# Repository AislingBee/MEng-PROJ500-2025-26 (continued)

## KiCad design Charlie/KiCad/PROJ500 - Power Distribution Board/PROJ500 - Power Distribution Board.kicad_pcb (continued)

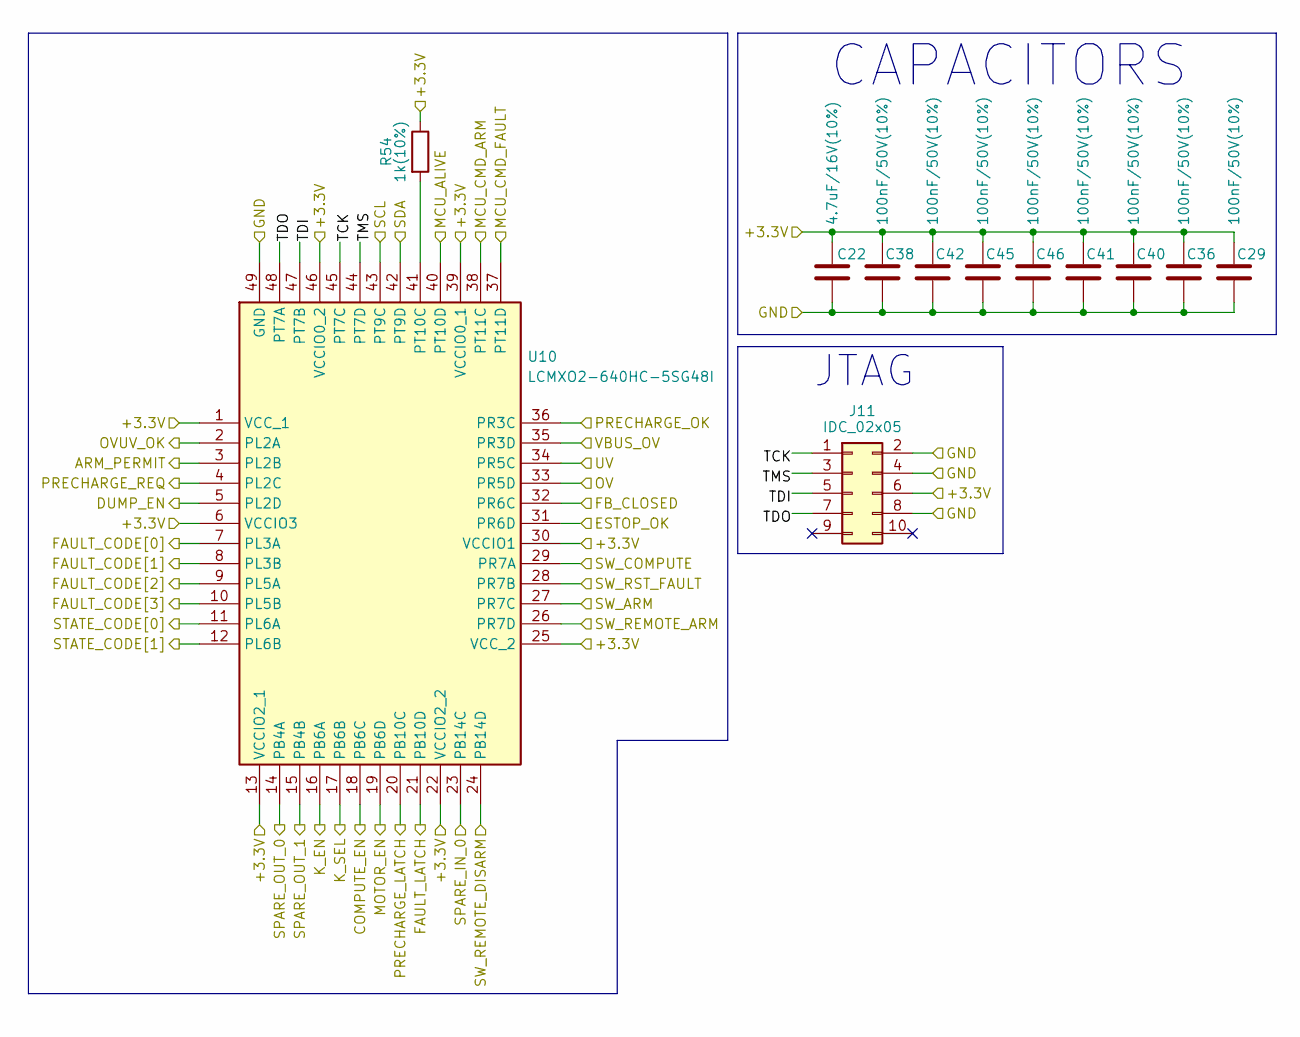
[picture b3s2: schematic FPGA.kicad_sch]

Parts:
C22: 4.7uF/16V(10%); C_0805_2012Metric
C29, C36, C38, C40, C41, C42, C45, C46: 100nF/50V(10%); C_0402_1005Metric
J11: IDC_02x05; IDC-Header_2x05_P2.54mm_Vertical
R54: 1k(10%); R_0402_1005Metric
U10: LCMXO2-640HC-5SG48I; QFN50P700X700X100-49N-D; Mouser Part Number 842-MXO2640HC5SG48I

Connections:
+3.3V: C22.1, C29.2, C36.2, C38.2, C40.2, C41.2, C42.2, C45.2, C46.2, J11.6, R54.1, U10.1 (VCC_1), U10.6 (VCCIO3), U10.13 (VCCIO2_1), U10.22 (VCCIO2_2), U10.25 (VCC_2), U10.30 (VCCIO1), U10.39 (VCCIO0_1), U10.46 (VCCIO0_2); also elsewhere on the board
/ARM_PERMIT: U10.3 (PL2B)
/BUS_OV: U10.35 (PR3D); also elsewhere on the board
/COMPUTE_EN: U10.18 (PB6C); also elsewhere on the board
/DUMP_EN: U10.5 (PL2D)
/ESTOP_OK_BUF: U10.31 (PR6D); also elsewhere on the board
/FAULT_LATCH: U10.21 (PB10D); also elsewhere on the board
/FPGA/PRECHARGE_REQ: U10.4 (PL2C)
/FPGA/SPARE_IN_0: U10.23 (PB14C)
/FPGA/TCK: J11.1, U10.45 (PT7C)
/FPGA/TDI: J11.5, U10.47 (PT7B)
/FPGA/TDO: J11.7, U10.48 (PT7A)
/FPGA/TMS: J11.3, U10.44 (PT7D)
/FPGA_FC_0: U10.7 (PL3A); also elsewhere on the board
/FPGA_FC_1: U10.8 (PL3B); also elsewhere on the board
/FPGA_FC_2: U10.9 (PL5A); also elsewhere on the board
/FPGA_FC_3: U10.10 (PL5B); also elsewhere on the board
/FPGA_SC_0: U10.11 (PL6A); also elsewhere on the board
/FPGA_SC_1: U10.12 (PL6B); also elsewhere on the board
/FPGA_SPARE_OUT_0: U10.14 (PB4A); also elsewhere on the board
/FPGA_SPARE_OUT_1: U10.15 (PB4B); also elsewhere on the board
/K_EN: U10.16 (PB6A); also elsewhere on the board
/K_SEL: U10.17 (PB6B); also elsewhere on the board
/MCU_ALIVE: U10.40 (PT10D); also elsewhere on the board
/MCU_CMD_ARM: U10.38 (PT11C); also elsewhere on the board
/MCU_CMD_FAULT: U10.37 (PT11D); also elsewhere on the board
/MOTOR_CONT_EN: U10.19 (PB6D); also elsewhere on the board
/MOTOR_CONT_FB: U10.32 (PR6C); also elsewhere on the board
/OVUV_OK: U10.2 (PL2A)
/PRECHARGE_LATCH: U10.20 (PB10C)
/PRECHARGE_OK: U10.36 (PR3C); also elsewhere on the board
/SCL: U10.43 (PT9C); also elsewhere on the board
/SDA: U10.42 (PT9D); also elsewhere on the board
/SOURCE_OV: U10.33 (PR5D); also elsewhere on the board
/SOURCE_UV: U10.34 (PR5C); also elsewhere on the board
/SW_ARM_BUF: U10.27 (PR7C); also elsewhere on the board
/SW_COMPUTE_BUF: U10.29 (PR7A); also elsewhere on the board
/SW_REMOTE_ARM_BUF: U10.26 (PR7D); also elsewhere on the board
/SW_REMOTE_DISARM_BUF: U10.24 (PB14D); also elsewhere on the board
/SW_RST_FAULT_BUF: U10.28 (PR7B); also elsewhere on the board
GND: C22.2, C29.1, C36.1, C38.1, C40.1, C41.1, C42.1, C45.1, C46.1, J11.2, J11.4, J11.8, U10.49 (GND); also elsewhere on the board
unnamed: R54.2, U10.41 (PT10C)

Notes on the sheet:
JTAG
CAPACITORS

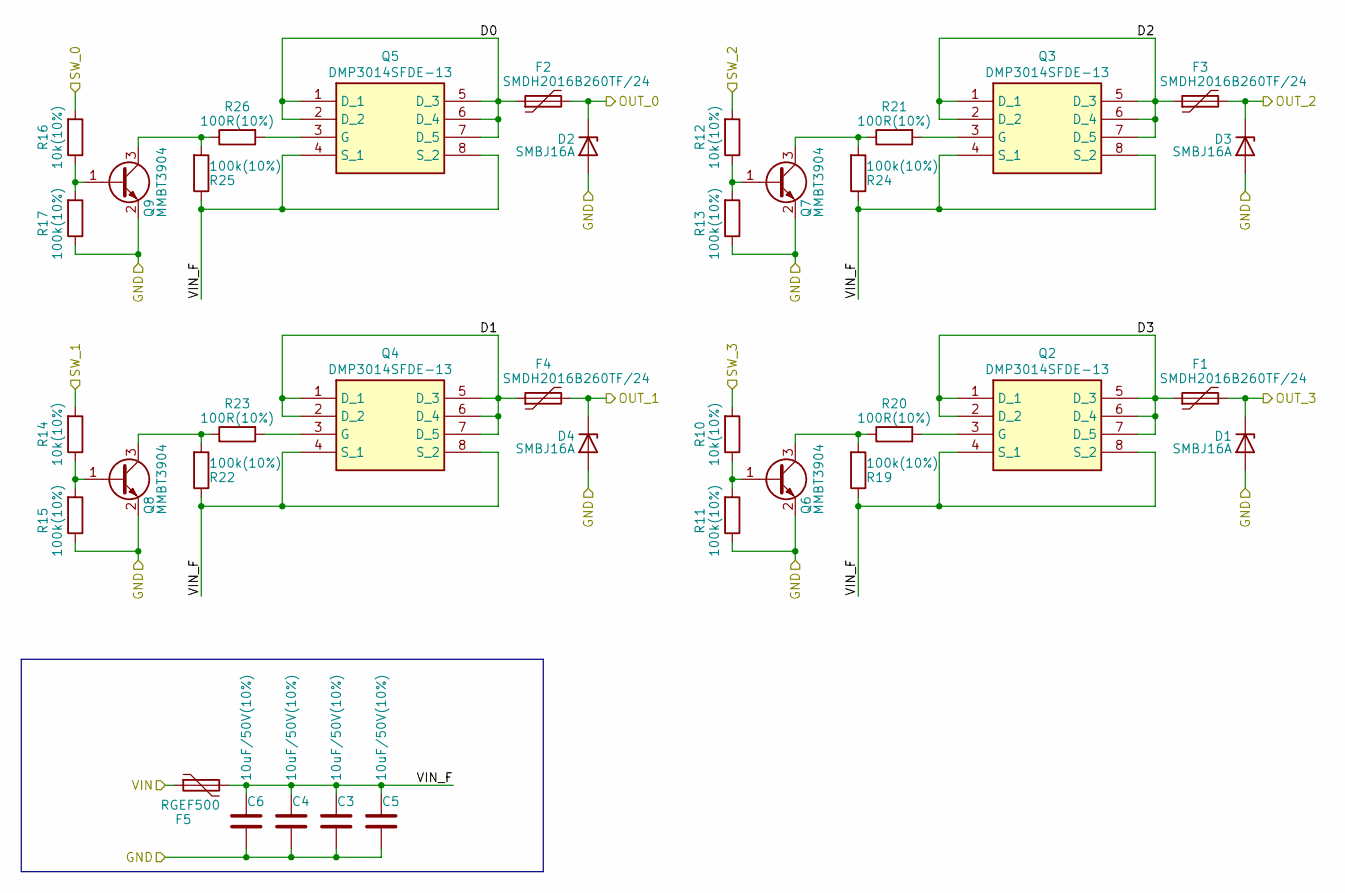
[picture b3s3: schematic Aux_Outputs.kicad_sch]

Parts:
C3, C4, C5, C6: 10uF/50V(10%); C_1206_3216Metric
D1, D2, D3, D4: SMBJ16A; D_SMB
F1, F2, F3, F4: SMDH2016B260TF/24; FUSC5141X160N
F5: RGEF500
Q2, Q3, Q4, Q5: DMP3014SFDE-13; DMP1022UFDEQ7; Manufacturer_Part_Number DMP3014SFDE-13
Q6, Q7, Q8, Q9: MMBT3904; SOT-23
R10, R12, R14, R16: 10k(10%); R_0402_1005Metric
R11, R13, R15, R17, R19, R22, R24, R25: 100k(10%); R_0402_1005Metric
R20, R21, R23, R26: 100R(10%); R_0402_1005Metric

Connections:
12V_SW: F5.1; also elsewhere on the board
/AUX_SW_0: R16.2; also elsewhere on the board
/AUX_SW_1: R14.2; also elsewhere on the board
/AUX_SW_2: R12.2; also elsewhere on the board
/AUX_SW_3: R10.2; also elsewhere on the board
/Aux Outputs/D0: F2.1, Q5.1 (D_1), Q5.2 (D_2), Q5.5 (D_3), Q5.6 (D_4), Q5.7 (D_5)
/Aux Outputs/D1: F4.1, Q4.1 (D_1), Q4.2 (D_2), Q4.5 (D_3), Q4.6 (D_4), Q4.7 (D_5)
/Aux Outputs/D2: F3.1, Q3.1 (D_1), Q3.2 (D_2), Q3.5 (D_3), Q3.6 (D_4), Q3.7 (D_5)
/Aux Outputs/D3: F1.1, Q2.1 (D_1), Q2.2 (D_2), Q2.5 (D_3), Q2.6 (D_4), Q2.7 (D_5)
/Aux Outputs/OUT_0: D2.1 (K), F2.2; also elsewhere on the board
/Aux Outputs/OUT_1: D4.1 (K), F4.2; also elsewhere on the board
/Aux Outputs/OUT_2: D3.1 (K), F3.2; also elsewhere on the board
/Aux Outputs/OUT_3: D1.1 (K), F1.2; also elsewhere on the board
/Aux Outputs/VIN_F: C3.1, C4.1, C5.1, C6.1, F5.2, Q2.4 (S_1), Q2.8 (S_2), Q3.4 (S_1), Q3.8 (S_2), Q4.4 (S_1), Q4.8 (S_2), Q5.4 (S_1), Q5.8 (S_2), R19.1, R22.1, R24.1, R25.1
GND: C3.2, C4.2, C5.2, C6.2, D1.2 (A), D2.2 (A), D3.2 (A), D4.2 (A), Q6.2 (E), Q7.2 (E), Q8.2 (E), Q9.2 (E), R11.1, R13.1, R15.1, R17.1; also elsewhere on the board
unnamed: Q2.3 (G), R20.2
unnamed: Q3.3 (G), R21.2
unnamed: Q4.3 (G), R23.2
unnamed: Q5.3 (G), R26.2
unnamed: Q6.1 (B), R10.1, R11.2
unnamed: Q6.3 (C), R19.2, R20.1
unnamed: Q7.1 (B), R12.1, R13.2
unnamed: Q7.3 (C), R21.1, R24.2
unnamed: Q8.1 (B), R14.1, R15.2
unnamed: Q8.3 (C), R22.2, R23.1
unnamed: Q9.1 (B), R16.1, R17.2
unnamed: Q9.3 (C), R25.2, R26.1

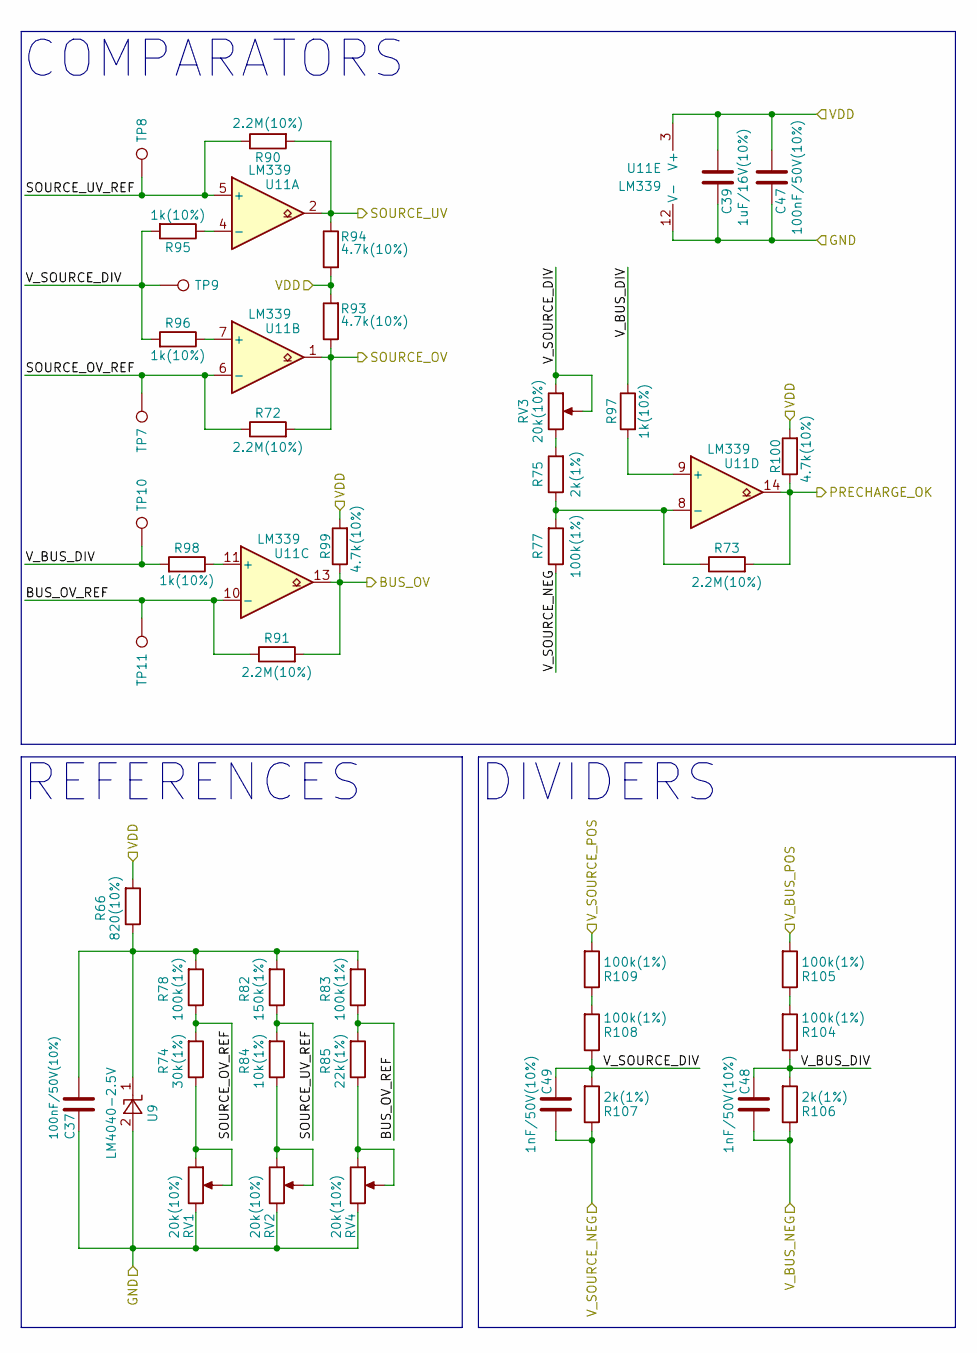
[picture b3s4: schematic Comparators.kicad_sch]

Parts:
C37, C47: 100nF/50V(10%); C_0402_1005Metric
C39: 1uF/16V(10%); C_0603_1608Metric
C48, C49: 1nF/50V(10%); C_0402_1005Metric
R66: 820(10%); R_0402_1005Metric
R72, R73, R90, R91: 2.2M(10%); R_0402_1005Metric
R74: 30k(1%); R_0402_1005Metric
R75, R106, R107: 2k(1%); R_0402_1005Metric
R77, R78, R83: 100k(1%); R_0402_1005Metric
R82: 150k(1%); R_0402_1005Metric
R84: 10k(1%); R_0402_1005Metric
R85: 22k(1%); R_0402_1005Metric
R93, R94, R99, R100: 4.7k(10%); R_0402_1005Metric
R95, R96, R97, R98: 1k(10%); R_0402_1005Metric
R104, R105, R108, R109: 100k(1%); R_0603_1608Metric
RV1, RV2, RV3, RV4: 20k(10%); Potentiometer_Bourns_3296Y_Vertical
TP7, TP8, TP9, TP10, TP11: TestPoint; TestPoint_Pad_D1.0mm
U9: LM4040-2.5V; TSOT-23; Part Number LM4040B25FTA
U11: LM339; TSSOP-14_4.4x5mm_P0.65mm

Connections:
+3.3VA: C39.2, C47.1, R66.2, R93.2, R94.2, R99.2, R100.2, U11.3 (V+); also elsewhere on the board
/BUS_OV: R91.2, R99.1, U11.13; also elsewhere on the board
/Comparators/BUS_OV_REF: R83.1, R85.2, R91.1, TP11.1, U11.10 (-)
/Comparators/SOURCE_OV_REF: R72.1, R74.2, R78.1, TP7.1, U11.6 (-)
/Comparators/SOURCE_UV_REF: R82.1, R84.2, R90.1, TP8.1, U11.5 (+)
/Comparators/V_BUS_DIV: C48.1, R97.1, R98.2, R104.1, R106.2, TP10.1
/Comparators/V_SOURCE_DIV: C49.1, R95.2, R96.2, R107.2, R108.1, RV3.1, RV3.2, TP9.1
/PRECHARGE_OK: R73.2, R100.1, U11.14; also elsewhere on the board
/SOURCE_OV: R72.2, R93.1, U11.1; also elsewhere on the board
/SOURCE_UV: R90.2, R94.1, U11.2; also elsewhere on the board
/V_BUS_POS: R105.2; also elsewhere on the board
/V_SENSE_NEG: C48.2, C49.2, R77.1, R106.1, R107.1; also elsewhere on the board
/V_SOURCE_POS: R109.2; also elsewhere on the board
GNDA: C37.2, C39.1, C47.2, RV1.3, RV2.3, RV4.3, U9.2 (A), U11.12 (V-); also elsewhere on the board
unnamed: R74.1, RV1.1, RV1.2
unnamed: R75.2, RV3.3
unnamed: R84.1, RV2.1, RV2.2
unnamed: R85.1, RV4.1, RV4.2
unnamed: R104.2, R105.1
unnamed: R108.2, R109.1
unnamed: C37.1, R66.1, R78.2, R82.2, R83.2, U9.1 (K)
unnamed: R95.1, U11.4 (-)
unnamed: R96.1, U11.7 (+)
unnamed: R98.1, U11.11 (+)
unnamed: R97.2, U11.9 (+)
unnamed: R73.1, R75.1, R77.2, U11.8 (-)

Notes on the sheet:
COMPARATORS
REFERENCES
DIVIDERS

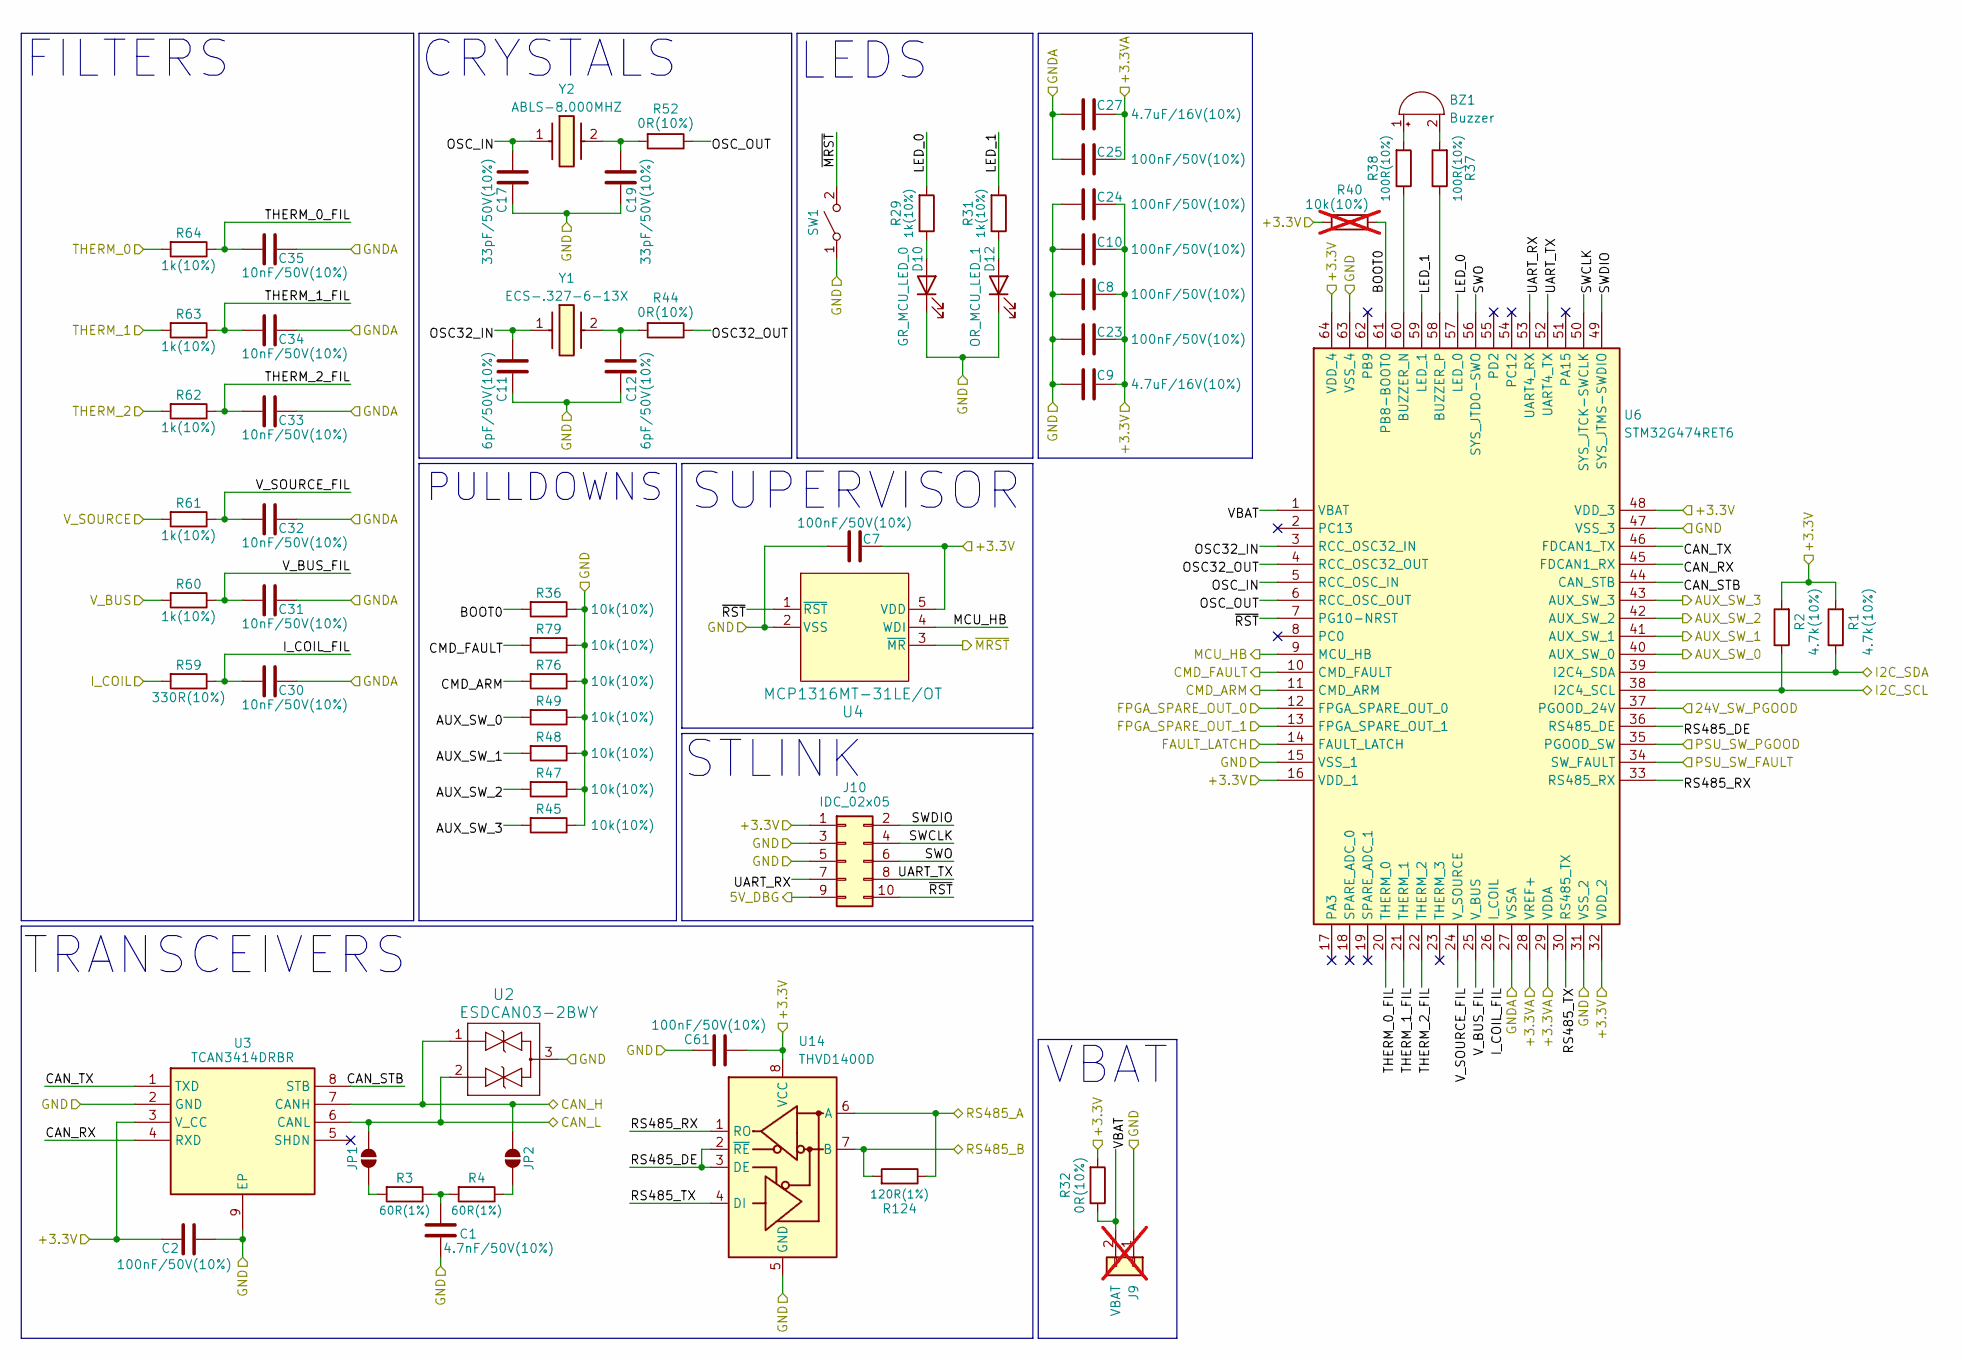
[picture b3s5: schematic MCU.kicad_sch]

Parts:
BZ1: Buzzer; C_Radial_D10.0mm_H12.5mm_P5.00mm
C1: 4.7nF/50V(10%); C_0402_1005Metric
C2, C7, C8, C10, C23, C24, C25, C61: 100nF/50V(10%); C_0402_1005Metric
C9, C27: 4.7uF/16V(10%); C_0805_2012Metric
C11, C12: 6pF/50V(10%); C_0402_1005Metric
C17, C19: 33pF/50V(10%); C_0402_1005Metric
C30, C31, C32, C33, C34, C35: 10nF/50V(10%); C_0402_1005Metric
D10: GR_MCU_LED_0; D_0805_2012Metric
D12: OR_MCU_LED_1; D_0805_2012Metric
J9: VBAT; PinHeader_1x02_P2.54mm_Vertical; Part Number 1-0201FBV0T; not fitted
J10: IDC_02x05; IDC-Header_2x05_P2.54mm_Vertical
JP1, JP2: SolderJumper_2_Open; SolderJumper-2_P1.3mm_Open_Pad1.0x1.5mm
R1, R2: 4.7k(10%); R_0402_1005Metric
R3, R4: 60R(1%); R_0402_1005Metric
R29, R31, R60, R61, R62, R63, R64: 1k(10%); R_0402_1005Metric
R32, R44, R52: 0R(10%); R_0402_1005Metric
R36, R45, R47, R48, R49, R76, R79: 10k(10%); R_0402_1005Metric
R37, R38: 100R(10%); R_0402_1005Metric
R40: 10k(10%); R_0402_1005Metric; not fitted
R59: 330R(10%); R_0402_1005Metric
R124: 120R(1%); R_0402_1005Metric
SW1: SW_SPST; SW_SPST_TS-1088-xR020
U2: ESDCAN03-2BWY; SOT-323_SC-70
U3: TCAN3414DRBR; VSON-8-1EP_3x3mm_P0.65mm_EP1.6x2.4mm; Mouser Part Number 595-TCAN3414DRBR
U4: MCP1316MT-31LE/OT; SOT-23-5
U6: STM32G474RET6; LQFP-64_10x10mm_P0.5mm
U14: THVD1400D; SOIC-8_3.9x4.9mm_P1.27mm
Y1: ECS-.327-6-13X; Crystal_DS26_D2.0mm_L6.0mm_Vertical; Mouser Part Number 520-ECS327-6-13-X
Y2: ABLS-8.000MHZ; ABLS8000MHZ20D3HT; Mouser Part Number 815-LS8000MHZ20D3HT

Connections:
+3.3V: C2.2, C7.1, C8.2, C9.1, C10.2, C23.2, C24.2, C61.1, J10.1, R1.2, R2.2, R32.2, R40.1, U3.3 (V_CC), U4.5 (VDD), U6.16 (VDD_1), U6.32 (VDD_2), U6.48 (VDD_3), U6.64 (VDD_4), U14.8 (VCC); also elsewhere on the board
+3.3VA: C25.2, C27.1, U6.28 (VREF+), U6.29 (VDDA); also elsewhere on the board
/5V_DBG: J10.9; also elsewhere on the board
/24V_SW_PGOOD: U6.37 (PGOOD_24V); also elsewhere on the board
/AUX_SW_0: R49.2, U6.40 (AUX_SW_0); also elsewhere on the board
/AUX_SW_1: R48.2, U6.41 (AUX_SW_1); also elsewhere on the board
/AUX_SW_2: R47.2, U6.42 (AUX_SW_2); also elsewhere on the board
/AUX_SW_3: R45.2, U6.43 (AUX_SW_3); also elsewhere on the board
/CAN_H: JP2.2 (B), U2.1, U3.7 (CANH); also elsewhere on the board
/CAN_L: JP1.2 (B), U2.2, U3.6 (CANL); also elsewhere on the board
/FAULT_LATCH: U6.14 (FAULT_LATCH); also elsewhere on the board
/FPGA_SPARE_OUT_0: U6.12 (FPGA_SPARE_OUT_0); also elsewhere on the board
/FPGA_SPARE_OUT_1: U6.13 (FPGA_SPARE_OUT_1); also elsewhere on the board
/I_COIL: R59.2; also elsewhere on the board
/MCU/BOOT0: R36.2, R40.2, U6.61 (PB8-BOOT0)
/MCU/CAN_RX: U3.4 (RXD), U6.45 (FDCAN1_RX)
/MCU/CAN_STB: U3.8 (STB), U6.44 (CAN_STB)
/MCU/CAN_TX: U3.1 (TXD), U6.46 (FDCAN1_TX)
/MCU/I_COIL_FIL: C30.1, R59.1, U6.26 (I_COIL)
/MCU/LED_0: R29.2, U6.57 (LED_0)
/MCU/LED_1: R31.2, U6.59 (LED_1)
/MCU/OSC32_IN: C11.2, U6.3 (RCC_OSC32_IN), Y1.1
/MCU/OSC32_OUT: R44.1, U6.4 (RCC_OSC32_OUT)
/MCU/OSC_IN: C17.2, U6.5 (RCC_OSC_IN), Y2.1
/MCU/OSC_OUT: R52.1, U6.6 (RCC_OSC_OUT)
/MCU/RS485_DE: U6.36 (RS485_DE), U14.2 (~RE), U14.3 (DE)
/MCU/RS485_RX: U6.33 (RS485_RX), U14.1 (RO)
/MCU/RS485_TX: U6.30 (RS485_TX), U14.4 (DI)
/MCU/SWCLK: J10.4, U6.50 (SYS_JTCK-SWCLK)
/MCU/SWDIO: J10.2, U6.49 (SYS_JTMS-SWDIO)
/MCU/SWO: J10.6, U6.56 (SYS_JTDO-SWO)
/MCU/THERM_0_FIL: C35.1, R64.1, U6.20 (THERM_0)
/MCU/THERM_1_FIL: C34.1, R63.1, U6.21 (THERM_1)
/MCU/THERM_2_FIL: C33.1, R62.1, U6.22 (THERM_2)
/MCU/UART_RX: J10.7, U6.53 (UART4_RX)
/MCU/UART_TX: J10.8, U6.52 (UART4_TX)
/MCU/VBAT: J9.2, R32.1, U6.1 (VBAT)
/MCU/V_BUS_FIL: C31.1, R60.1, U6.25 (V_BUS)
/MCU/V_SOURCE_FIL: C32.1, R61.1, U6.24 (V_SOURCE)
/MCU/~RST: J10.10, U4.1 (~RST), U6.7 (PG10-NRST)
/MCU_ALIVE: U4.4 (WDI), U6.9 (MCU_HB); also elsewhere on the board
/MCU_CMD_ARM: R76.2, U6.11 (CMD_ARM); also elsewhere on the board
/MCU_CMD_FAULT: R79.2, U6.10 (CMD_FAULT); also elsewhere on the board
/MCU_NRST: SW1.2 (B), U4.3 (~MR)
/PSU_SW_FAULT: U6.34 (SW_FAULT); also elsewhere on the board
/PSU_SW_PGOOD: U6.35 (PGOOD_SW); also elsewhere on the board
/RS485_A: R124.1, U14.6 (A); also elsewhere on the board
/RS485_B: R124.2, U14.7 (B); also elsewhere on the board
/SCL: R2.1, U6.38 (I2C4_SCL); also elsewhere on the board
/SDA: R1.1, U6.39 (I2C4_SDA); also elsewhere on the board
/THERM_0: R64.2; also elsewhere on the board
/THERM_1: R63.2; also elsewhere on the board
/THERM_2: R62.2; also elsewhere on the board
/V_BUS_DIV: R60.2; also elsewhere on the board
/V_SOURCE_DIV: R61.2; also elsewhere on the board
GND: C1.1, C2.1, C7.2, C8.1, C9.2, C10.1, C11.1, C12.1, C17.1, C19.1, C23.1, C24.1, C61.2, D10.1 (K), D12.1 (K), J9.1, J10.3, J10.5, R36.1, R45.1, R47.1, R48.1, R49.1, R76.1, R79.1, SW1.1 (A), U2.3, U3.2 (GND), U3.9 (EP), U4.2 (VSS), U6.15 (VSS_1), U6.31 (VSS_2), U6.47 (VSS_3), U6.63 (VSS_4), U14.5 (GND); also elsewhere on the board
GNDA: C25.1, C27.2, C30.2, C31.2, C32.2, C33.2, C34.2, C35.2, U6.27 (VSSA); also elsewhere on the board
unnamed: BZ1.1 (+), R38.2
unnamed: BZ1.2 (-), R37.2
unnamed: C1.2, R3.1, R4.2
unnamed: C12.2, R44.2, Y1.2
unnamed: C19.2, R52.2, Y2.2
unnamed: D10.2 (A), R29.1
unnamed: D12.2 (A), R31.1
unnamed: JP1.1 (A), R3.2
unnamed: JP2.1 (A), R4.1
unnamed: R38.1, U6.60 (BUZZER_N)
unnamed: R37.1, U6.58 (BUZZER_P)

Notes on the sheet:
TRANSCEIVERS
LEDS
STLINK
SUPERVISOR
CRYSTALS
FILTERS
VBAT
PULLDOWNS

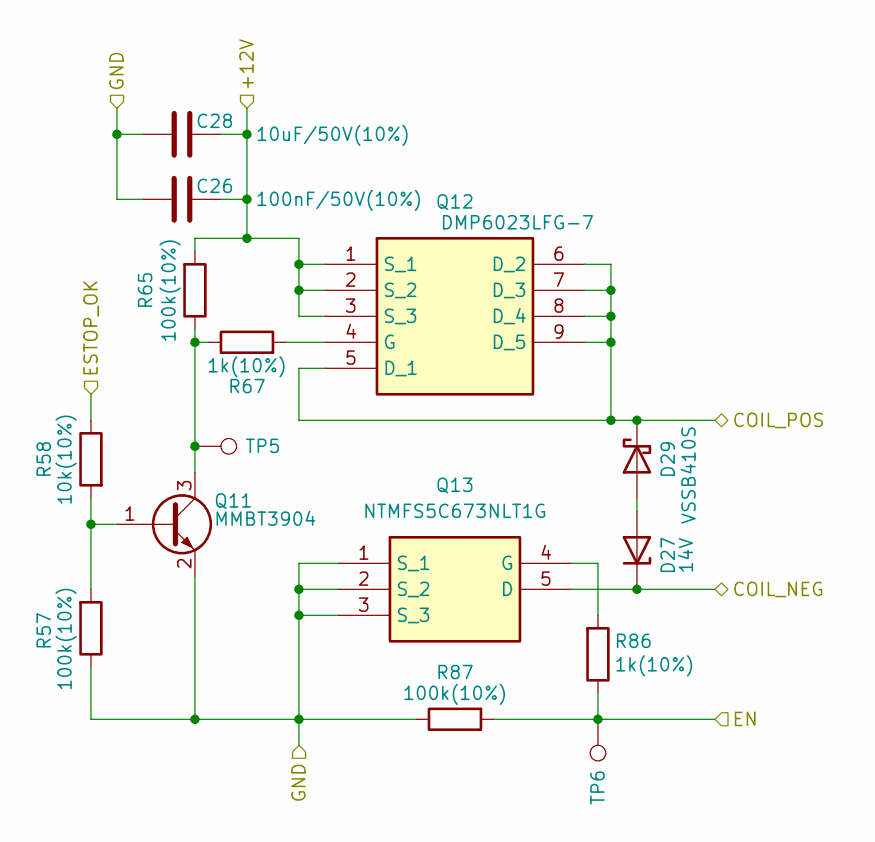
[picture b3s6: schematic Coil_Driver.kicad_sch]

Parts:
C26: 100nF/50V(10%); C_0402_1005Metric
C28: 10uF/50V(10%); C_1206_3216Metric
D27: 14V; D_SOD-123
D29: VSSB410S; D_SMB
Q11: MMBT3904; SOT-23
Q12: DMP6023LFG-7; DMP4013LFG7; Mouser Part Number 621-DMP6023LFG-7
Q13: NTMFS5C673NLT1G; ONSemi_SO-8FL_488AA; Mouser Part Number 863-NTMFS5C673NLT1G
R57, R65, R87: 100k(10%); R_0402_1005Metric
R58: 10k(10%); R_0402_1005Metric
R67, R86: 1k(10%); R_0402_1005Metric
TP5, TP6: TestPoint; TestPoint_Pad_D1.0mm

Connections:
+12V: C26.1, C28.2, Q12.1 (S_1), Q12.2 (S_2), Q12.3 (S_3), R65.2; also elsewhere on the board
/Coil Driver/COIL_NEG: D27.1 (K), Q13.5 (D); also elsewhere on the board
/ESTOP_OK_BUF: R58.1; also elsewhere on the board
/MOTOR_COIL_POS: D29.1 (K), Q12.5 (D_1), Q12.6 (D_2), Q12.7 (D_3), Q12.8 (D_4), Q12.9 (D_5); also elsewhere on the board
/MOTOR_CONT_EN: R86.1, R87.2, TP6.1; also elsewhere on the board
GND: C26.2, C28.1, Q11.2 (E), Q13.1 (S_1), Q13.2 (S_2), Q13.3 (S_3), R57.1, R87.1; also elsewhere on the board
unnamed: D27.2 (A), D29.2 (A)
unnamed: Q11.1 (B), R57.2, R58.2
unnamed: Q11.3 (C), R65.1, R67.1, TP5.1
unnamed: Q12.4 (G), R67.2
unnamed: Q13.4 (G), R86.2

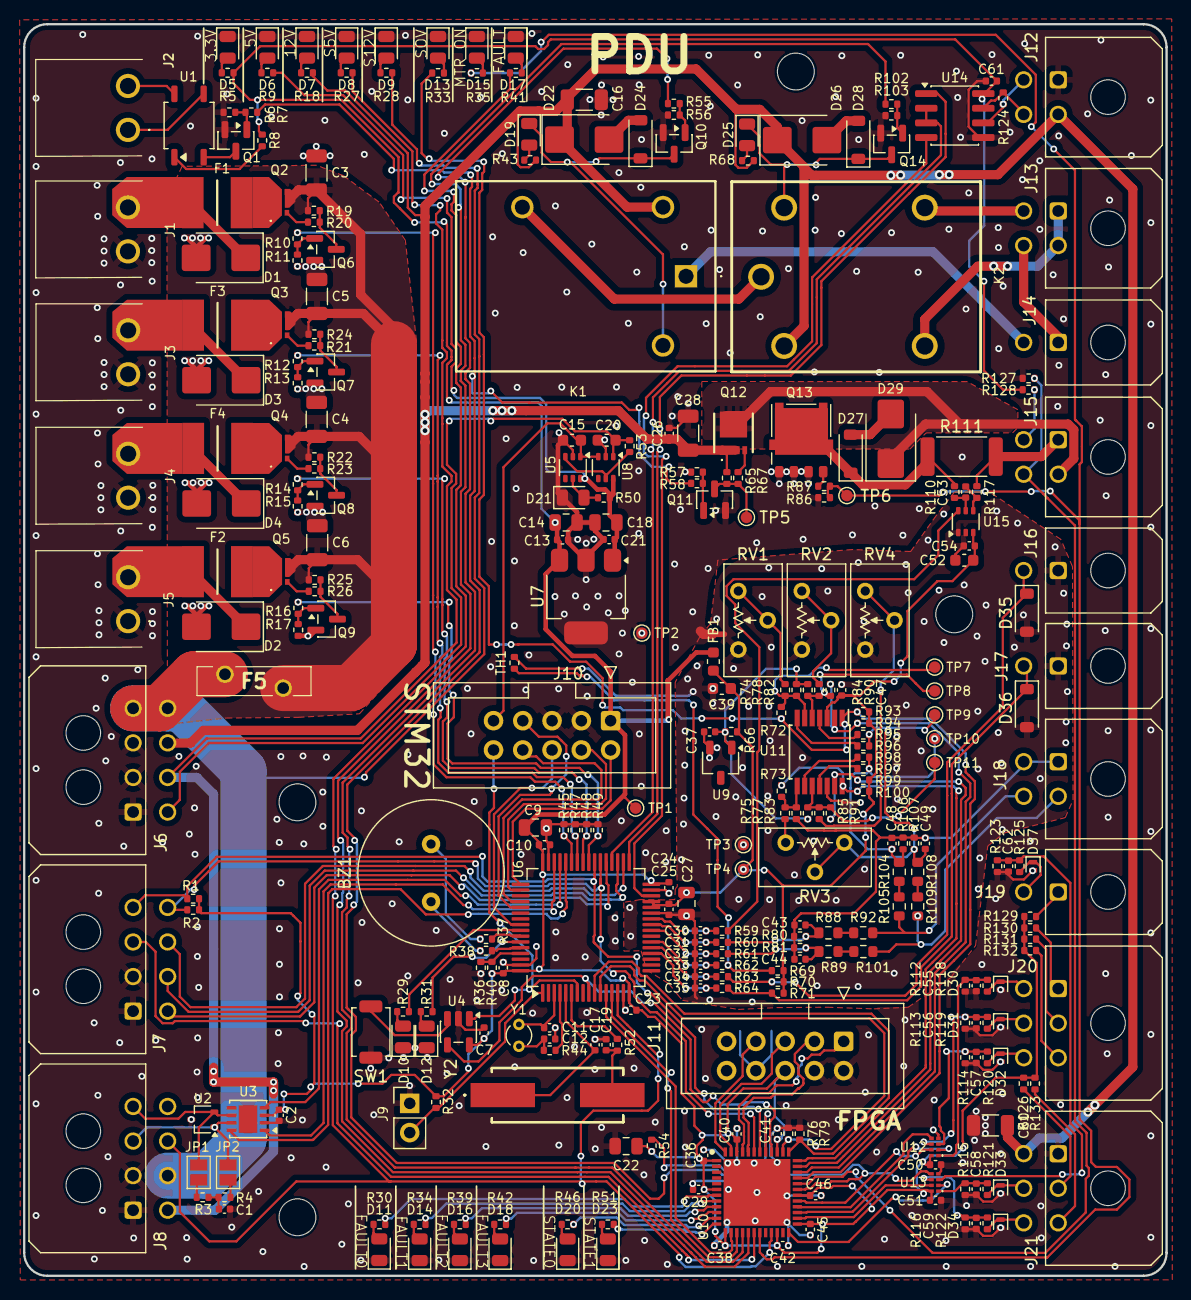
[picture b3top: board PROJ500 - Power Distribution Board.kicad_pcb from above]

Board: 2 copper layers, 99.1 x 108.6 mm, 317 parts (0 on the bottom side), 205 nets.

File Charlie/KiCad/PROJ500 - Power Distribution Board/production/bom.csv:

Designator,Footprint,Quantity,Value,LCSC Part #
BZ1,C_Radial_D10.0mm_H12.5mm_P5.00mm,1,Buzzer,
C1,0402,1,4.7nF/50V(10%),
"C10, C13, C2, C21, C23, C24, C25, C26, C29, C36, C37, C38, C40, C41, C42, C45, C46, C47, C50, C51, C54, C61, C7, C8",0402,24,100nF/50V(10%),
"C11, C12",0402,2,6pF/50V(10%),
"C14, C18, C22, C27, C9",0805,5,4.7uF/16V(10%),
"C15, C20, C39",0603,3,1uF/16V(10%),
"C16, C28, C3, C4, C5, C6, C60",1206,7,10uF/50V(10%),
"C17, C19",0402,2,33pF/50V(10%),
"C30, C31, C32, C33, C34, C35, C55, C56, C57, C58, C59, C62",0402,12,10nF/50V(10%),
"C43, C44, C48, C49",0402,4,1nF/50V(10%),
C52,0603,1,2.2uF/10V(10%),
C53,0402,1,100pF/50V(10%),
"D1, D2, D3, D4",D_SMB,4,SMBJ16A,
D10,0805,1,GR_MCU_LED_0,
D11,0805,1,RE_FAULT_0,
D12,0805,1,OR_MCU_LED_0,
D13,0805,1,RE_OV,
D14,0805,1,RE_FAULT_1,
D15,0805,1,OR_MOTOR,
D16,0805,1,RE_FAULT_2,
D17,0805,1,RE_FAULT,
D18,0805,1,RE_FAULT_3,
D19,0805,1,GR_K_EN,
D20,0805,1,GR_STATE_0,
D21,0805,1,OR_DBG_PWR,
"D22, D26, D29",D_SMB,3,VSSB410S,
D23,0805,1,GR_STATE_1,
"D24, D27, D28",D_SOD-123,3,14V,
D25,0805,1,GR_K_SEL,
"D30, D31, D32, D33, D34, D37",D_SOD-882,6,AQ3041,
"D35, D36",D_SOD-123,2,3.3V,
D5,0805,1,GR_3.3V,
D6,0805,1,GR_5V,
D7,0805,1,GR_12V,
D8,0805,1,GR_5VSW,
D9,0805,1,GR_12VSW,
"F1, F2, F3, F4",FUSC5141X160N,4,SMDH2016B260TF,
F5,RGEF500,1,RGEF500,
FB1,0603,1,120R/3A,
J1,TBP02R138102BE,1,AUX_OUT_3,
"J10, J11",IDC-Header_2x05_P2.54mm_Vertical,2,IDC_02x05,
J12,Molex_Micro-Fit_3.0_43045-0400_2x02_P3.00mm_Horizontal,1,RS485,
J13,Molex_Micro-Fit_3.0_43045-0400_2x02_P3.00mm_Horizontal,1,VIN,
J14,Molex_Micro-Fit_3.0_43045-0200_2x01_P3.00mm_Horizontal,1,EXT_RES,
J15,Molex_Micro-Fit_3.0_43045-0400_2x02_P3.00mm_Horizontal,1,MOTOR_CONT,
J16,Molex_Micro-Fit_3.0_43045-0200_2x01_P3.00mm_Horizontal,1,THERM_1,
J17,Molex_Micro-Fit_3.0_43045-0200_2x01_P3.00mm_Horizontal,1,THERM_0,
J18,Molex_Micro-Fit_3.0_43045-0400_2x02_P3.00mm_Horizontal,1,V_SENSE,
J19,Molex_Micro-Fit_3.0_43045-0200_2x01_P3.00mm_Horizontal,1,ESTOP_OK,
J2,TBP02R138102BE,1,ESTOP_REP,
J20,Molex_Micro-Fit_3.0_43045-0600_2x03_P3.00mm_Horizontal,1,SW_MISC,
J21,Molex_Micro-Fit_3.0_43045-0600_2x03_P3.00mm_Horizontal,1,SW_REMOTE_ARM,
J3,TBP02R138102BE,1,AUX_OUT_2,
J4,TBP02R138102BE,1,AUX_OUT_1,
J5,TBP02R138102BE,1,AUX_OUT_0,
J6,Molex_Micro-Fit_3.0_43045-0800_2x04_P3.00mm_Horizontal,1,PSU_B2B_PWR,
J7,Molex_Micro-Fit_3.0_43045-0800_2x04_P3.00mm_Horizontal,1,PSU_B2B_SIG,
J8,Molex_Micro-Fit_3.0_43045-0800_2x04_P3.00mm_Horizontal,1,RCU_B2B,
K1,G5LE1A4DC12,1,G5LE-1A4-DC12,
K2,G5LE-14_SPDT,1,G5LE-14-ASI_DC12,
"Q1, Q10, Q11, Q14, Q6, Q7, Q8, Q9",SOT-23,8,MMBT3904,
Q12,DMP4013LFG7,1,DMP6023LFG-7,
Q13,ONSemi_SO-8FL_488AA,1,NTMFS5C673NLT1G,
"Q2, Q3, Q4, Q5",DMP1022UFDEQ7,4,DMP3014SFDE-13,
"R1, R100, R2, R93, R94, R99",0402,6,4.7k(10%),
"R10, R12, R14, R16, R18, R28, R36, R43, R45, R47, R48, R49, R53, R58, R68, R7, R76, R79",0402,18,10k(10%),
"R101, R104, R105, R108, R109, R88, R89, R92",0603,8,100k(1%),
"R102, R55, R59",0402,3,330R(10%),
"R103, R11, R112, R113, R114, R115, R116, R123, R13, R15, R17, R19, R22, R24, R25, R56, R57, R6, R65, R87",0402,20,100k(10%),
"R106, R107, R75",0402,3,2k(1%),
"R110, R117",0402,2,4.7R(1%),
R111,2512,1,10m/1W(1%),
"R118, R119, R120, R121, R122, R125, R126, R128, R129, R130, R131, R132, R133, R29, R30, R31, R33, R34, R35, R39, R41, R42, R46, R5, R51, R54, R60, R61, R62, R63, R64, R67, R86, R95, R96, R97, R98",0402,37,1k(10%),
R124,0402,1,120R(1%),
"R127, R69, R70, R71, R84",0402,5,10k(1%),
"R20, R21, R23, R26, R37, R38",0402,6,100R(10%),
"R27, R9",0402,2,1.8k(10%),
"R3, R4",0402,2,60R(1%),
"R32, R44, R52",0402,3,0R(10%),
R50,0402,1,3.3k(10%),
R66,0402,1,820(10%),
"R72, R73, R90, R91",0402,4,2.2M(10%),
R74,0402,1,30k(1%),
"R77, R78, R83",0402,3,100k(1%),
R8,0402,1,510R(10%),
"R80, R81",0402,2,5.6k(1%),
R82,0402,1,150k(1%),
R85,0402,1,22k(1%),
"RV1, RV2, RV3, RV4",Potentiometer_Bourns_3296Y_Vertical,4,20k(10%),
SW1,SW_SPST_TS-1088-xR020,1,SW_SPST,
TH1,0402,1,NTC/10K,
"TP1, TP10, TP11, TP2, TP3, TP4, TP5, TP6, TP7, TP8, TP9",TestPoint_Pad_D1.0mm,11,TestPoint,
U1,SOP-4_3.8x4.1mm_P2.54mm,1,CPC1017N,
U10,QFN50P700X700X100-49N-D,1,LCMXO2-640HC-5SG48I,
U11,TSSOP-14_4.4x5mm_P0.65mm,1,LM339,
"U12, U13",XC7WT14GT115,2,"74LVC3G17GT,115",
U14,SOIC-8_3.9x4.9mm_P1.27mm,1,THVD1400D,
U15,SOT-363_SC-70-6,1,MCP6C26T-050E_LTY,
U2,SOT-323_SC-70,1,ESDCAN03-2BWY,
U3,VSON-8-1EP_3x3mm_P0.65mm_EP1.6x2.4mm,1,TCAN3414DRBR,
U4,SOT-23-5,1,MCP1316MT-31LE/OT,
"U5, U8",SOT-363_SC-70-6,2,LM66100DCK,
U6,LQFP-64_10x10mm_P0.5mm,1,STM32G474RET6,
U7,SOT-223,1,AP2114HA-3.3TRG1,
U9,TSOT-23,1,LM4040-2.5V,
Y1,Crystal_DS26_D2.0mm_L6.0mm_Vertical,1,ECS-.327-6-13X,
Y2,ABLS8000MHZ20D3HT,1,ABLS-8.000MHZ,

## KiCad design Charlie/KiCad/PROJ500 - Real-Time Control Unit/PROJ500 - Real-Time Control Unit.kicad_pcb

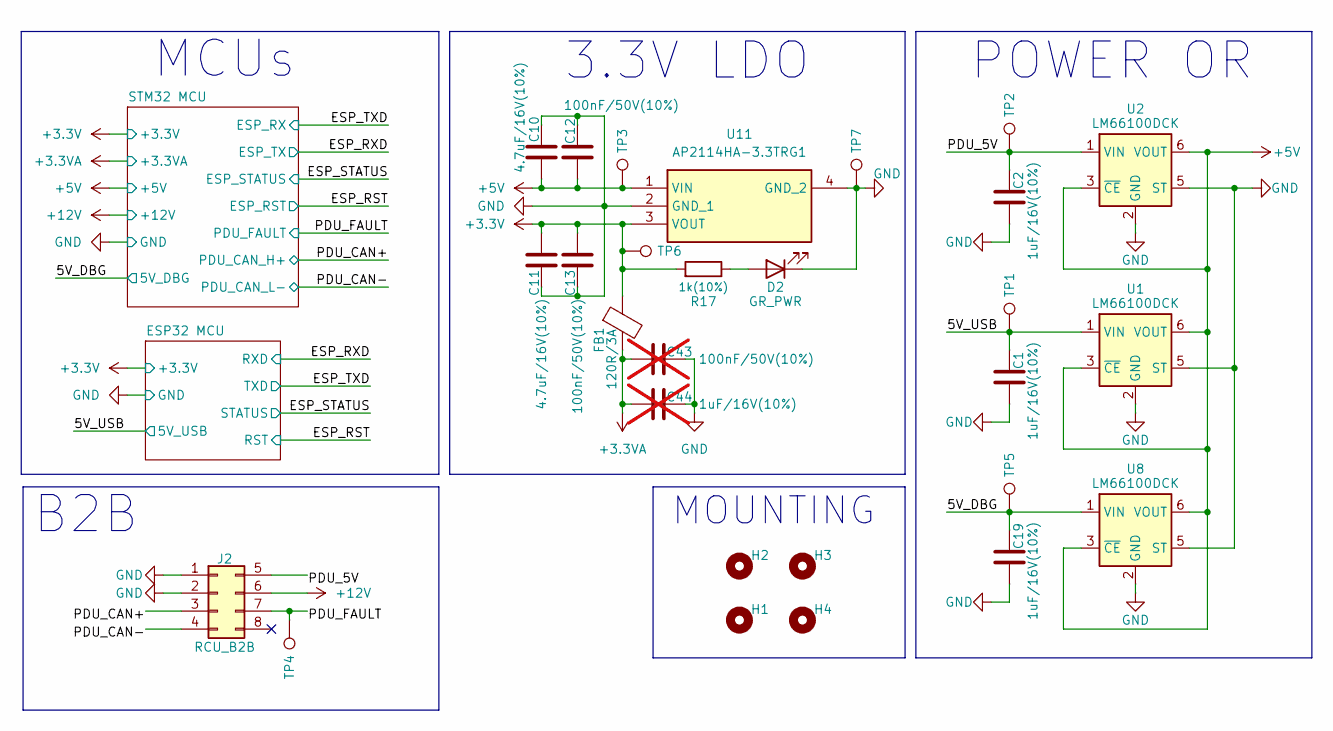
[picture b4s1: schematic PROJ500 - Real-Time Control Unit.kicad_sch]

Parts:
C1, C2, C19: 1uF/16V(10%); C_0603_1608Metric
C10, C11: 4.7uF/16V(10%); C_0805_2012Metric
C12, C13: 100nF/50V(10%); C_0402_1005Metric
C43: 100nF/50V(10%); C_0402_1005Metric; not fitted
C44: 1uF/16V(10%); C_0603_1608Metric; not fitted
D2: GR_PWR; D_0805_2012Metric
FB1: 120R/3A; L_0603_1608Metric
H1, H2, H3, H4: MountingHole; MountingHole_3.2mm_M3
J2: RCU_B2B; Molex_Micro-Fit_3.0_43045-0800_2x04_P3.00mm_Horizontal
R17: 1k(10%); R_0402_1005Metric
TP1, TP2, TP3, TP4, TP5, TP6, TP7: TestPoint; TestPoint_Pad_D1.0mm
U1, U2, U8: LM66100DCK; SOT-363_SC-70-6
U11: AP2114HA-3.3TRG1; SOT-223; Mouser Part Number 621-AP2114HA-3.3TRG1

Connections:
+3.3V: C11.2, C13.1, FB1.1, R17.2, TP6.1, U11.3 (VOUT); also elsewhere on the board
+3.3VA: C43.1, C44.2, FB1.2; also elsewhere on the board
+5V: C10.2, C12.1, TP3.1, U1.3 (~CE), U1.6 (VOUT), U2.3 (~CE), U2.6 (VOUT), U8.3 (~CE), U8.6 (VOUT), U11.1 (VIN); also elsewhere on the board
+12V: J2.6; also elsewhere on the board
/5V_DBG: C19.1, TP5.1, U8.1 (VIN); also elsewhere on the board
/5V_USB: C1.1, TP1.1, U1.1 (VIN); also elsewhere on the board
/PDU_5V: C2.1, J2.5, TP2.1, U2.1 (VIN)
/PDU_CAN+: J2.3; also elsewhere on the board
/PDU_CAN-: J2.4; also elsewhere on the board
/PDU_FAULT: J2.7, TP4.1; also elsewhere on the board
GND: C1.2, C2.2, C10.1, C11.1, C12.2, C13.2, C19.2, C43.2, C44.1, D2.1 (K), J2.1, J2.2, TP7.1, U1.2 (GND), U1.5 (ST), U2.2 (GND), U2.5 (ST), U8.2 (GND), U8.5 (ST), U11.2 (GND_1), U11.4 (GND_2); also elsewhere on the board
unnamed: D2.2 (A), R17.1

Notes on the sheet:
POWER OR
MCUs
MOUNTING
B2B
3.3V LDO
